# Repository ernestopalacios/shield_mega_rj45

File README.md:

shiel_mega_rj45
===============

Shield for arduino mega I/O using RJ45 connectors

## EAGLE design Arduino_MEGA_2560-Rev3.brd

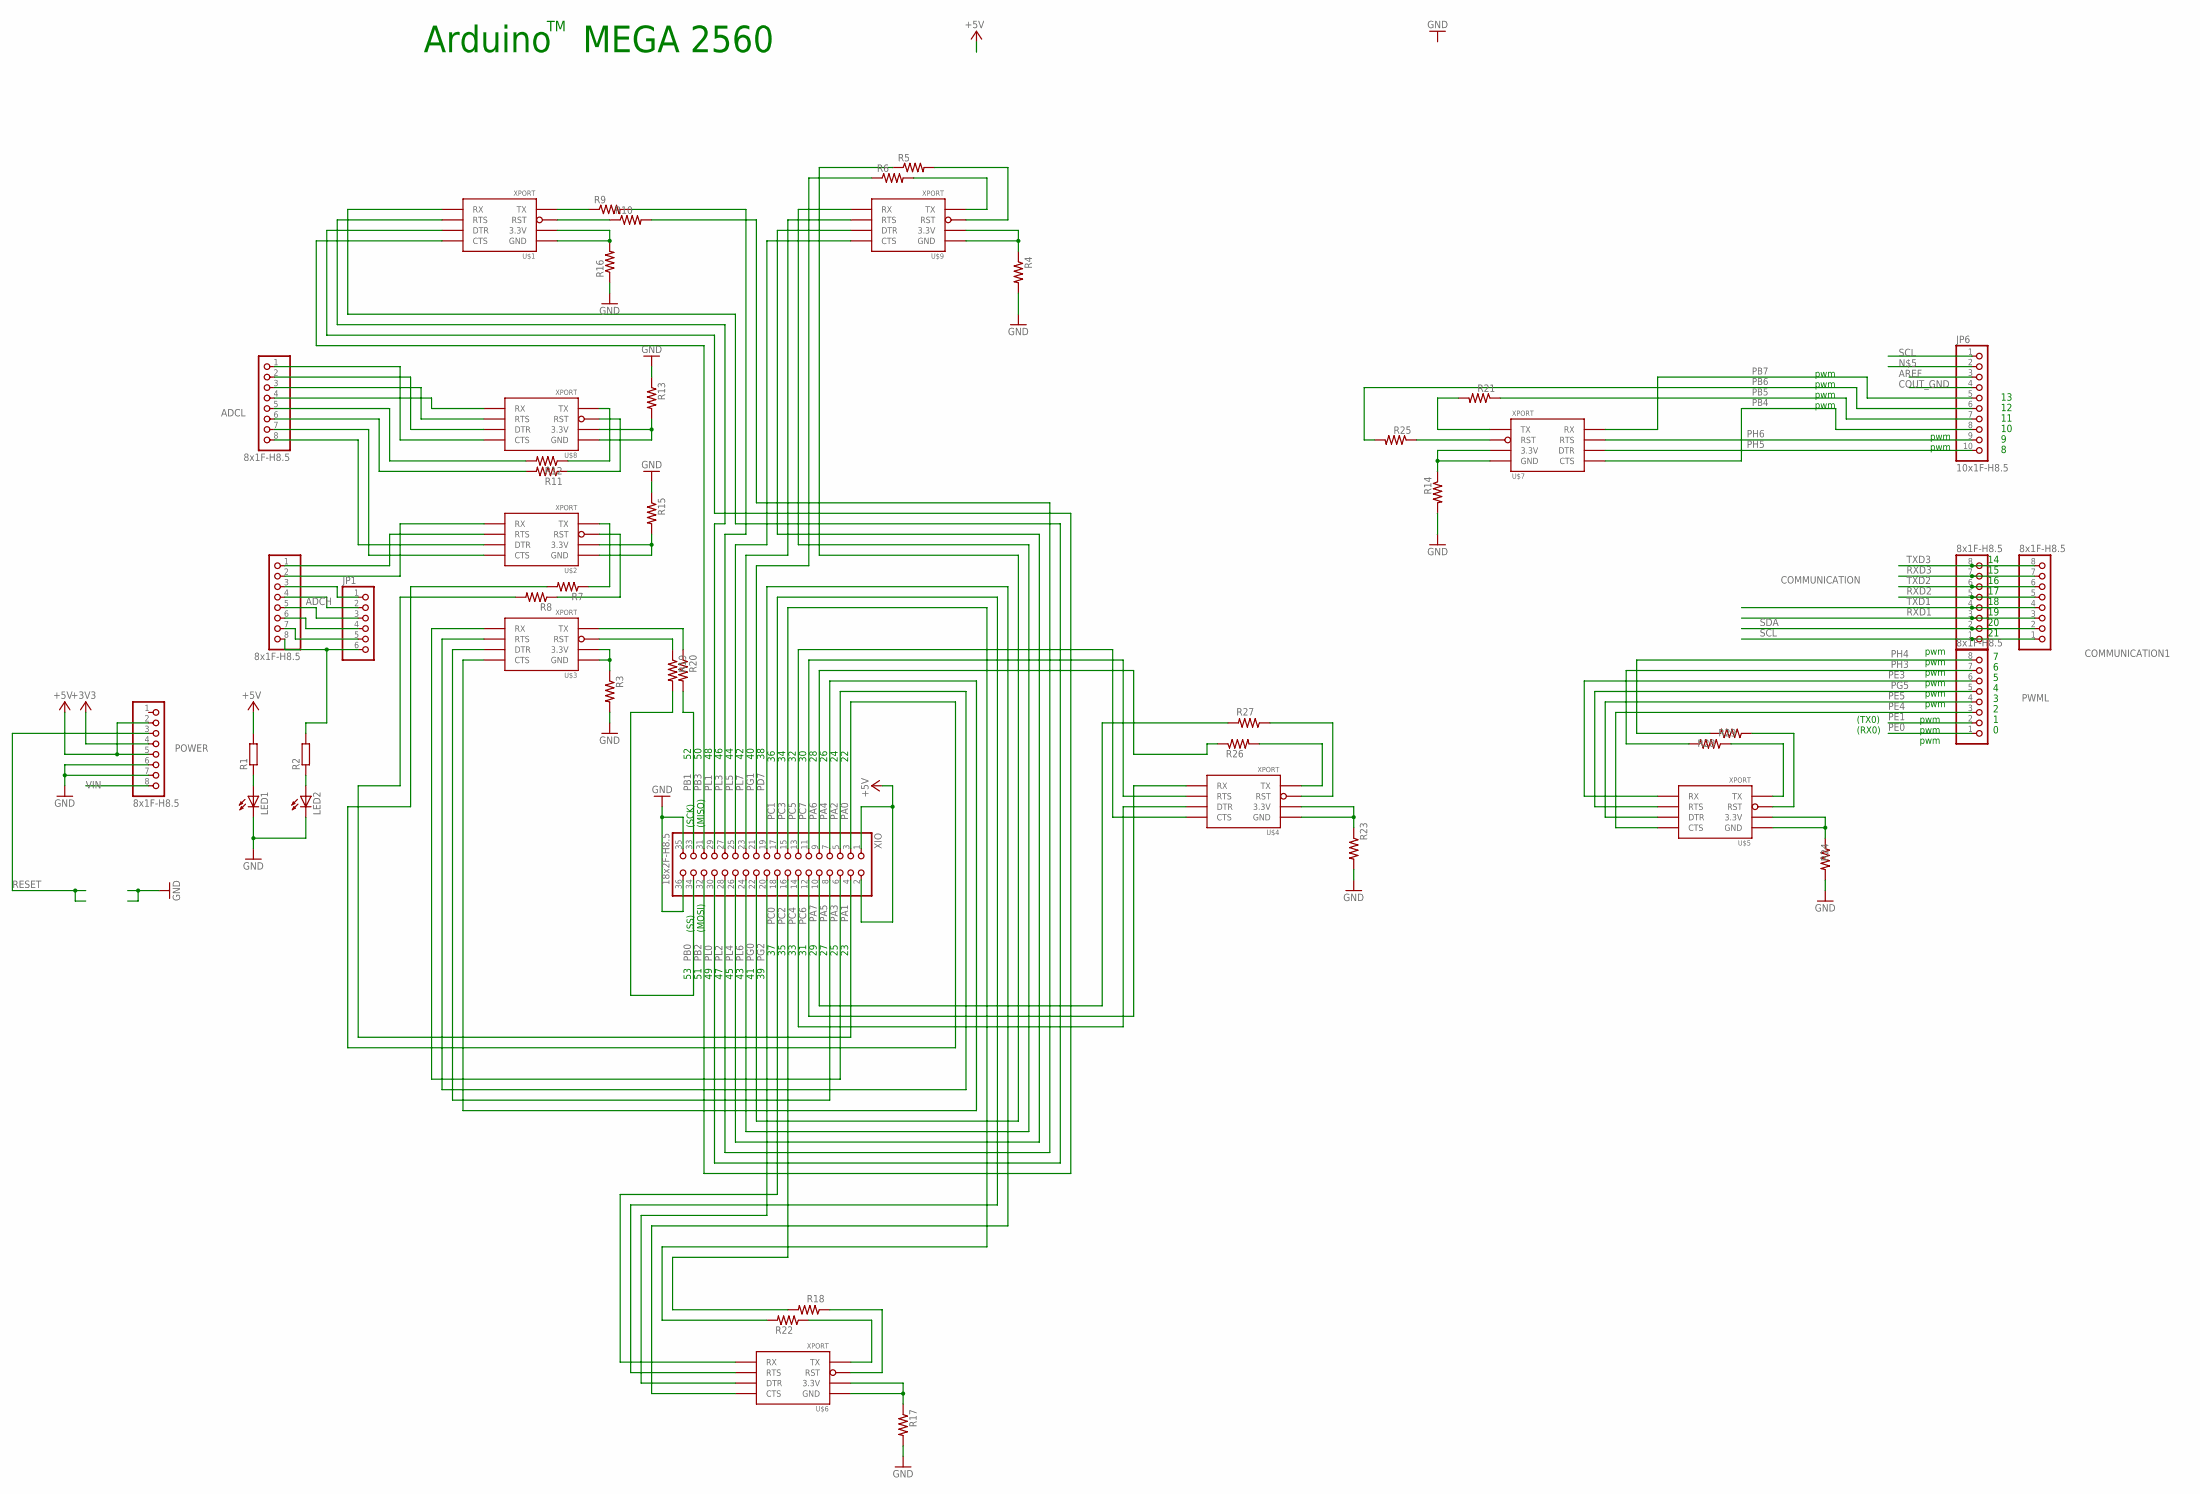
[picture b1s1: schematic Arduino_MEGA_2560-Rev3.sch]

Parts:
ADCH: 8x1F-H8.5; 1X08
ADCL: 8x1F-H8.5; 1X08
COMMUNICATION, COMMUNICATION1: 8x1F-H8.5; 1X08
JP1: PINHD-1X6; 1X06
JP6: 10x1F-H8.5; 1X10
LED1, LED2: LEDCHIPLED_1206; CHIPLED_1206
POWER: 8x1F-H8.5; 1X08
PWML: 8x1F-H8.5; 1X08
R1, R2: R-EU_M1206; M1206
R3, R7, R8, R11, R12, R13, R14, R15, R19, R20: R-US_0207/10; 0207/10
R4, R5, R6, R9, R10, R16, R17, R18, R22, R23, R24, R26, R27, R28, R29: R-US_0207/15; 0207/15
R21, R25: R-US_0207/2V; 0207/2V
U$1, U$2, U$3, U$4, U$5, U$6, U$7, U$8, U$9: XPORT
XIO: 18x2F-H8.5; 2X18

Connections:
+3V3: POWER.4
+5V: POWER.2, POWER.5, R1.2, XIO.1, XIO.2
AREF: JP6.3
COUT_GND: JP6.4, LED1.C, LED2.C, POWER.6, POWER.7, R3.2, R4.2, R13.1, R14.2, R15.1, R16.1, R17.2, R23.2, R24.2, XIO.35, XIO.36
unnamed: LED1.A, R1.1
unnamed: LED2.A, R2.1
unnamed: ADCH.1, U$2.P6 (RTS)
unnamed: ADCH.2, U$2.P5 (RX)
unnamed: R14.1, U$7.P1 (GND), U$7.P2 (3.3V)
unnamed: ADCL.1, U$8.P8 (CTS)
unnamed: ADCL.2, U$8.P7 (DTR)
unnamed: ADCL.3, U$8.P6 (RTS)
unnamed: ADCH.3, JP1.1
unnamed: ADCL.4, U$8.P5 (RX)
unnamed: ADCL.5, R12.2
unnamed: ADCL.6, R11.2
unnamed: ADCL.7, U$2.P8 (CTS)
unnamed: ADCL.8, U$2.P7 (DTR)
unnamed: R15.2, U$2.P1 (GND), U$2.P2 (3.3V)
unnamed: R3.1, U$3.P1 (GND), U$3.P2 (3.3V)
unnamed: R4.1, U$9.P1 (GND), U$9.P2 (3.3V)
unnamed: R5.2, U$9.P3 (RST)
unnamed: R6.2, U$9.P4 (TX)
unnamed: ADCH.4, JP1.2
unnamed: ADCH.5, JP1.3
unnamed: ADCH.6, JP1.4
unnamed: ADCH.7, JP1.5
unnamed: ADCH.8, JP1.6, R2.2
unnamed: R16.2, U$1.P1 (GND), U$1.P2 (3.3V)
unnamed: R10.1, U$1.P3 (RST)
unnamed: R9.1, U$1.P4 (TX)
unnamed: R17.1, U$6.P1 (GND), U$6.P2 (3.3V)
unnamed: R7.1, U$2.P4 (TX)
unnamed: R8.1, U$2.P3 (RST)
unnamed: R22.1, U$6.P4 (TX)
unnamed: R18.1, U$6.P3 (RST)
unnamed: R24.1, U$5.P1 (GND), U$5.P2 (3.3V)
unnamed: R23.1, U$4.P1 (GND), U$4.P2 (3.3V)
unnamed: R19.1, U$3.P3 (RST)
unnamed: R20.2, XIO.33
unnamed: R21.2, U$7.P4 (TX)
unnamed: R25.1, U$7.P3 (RST)
unnamed: R28.1, U$5.P4 (TX)
unnamed: R29.1, U$5.P3 (RST)
unnamed: R26.2, U$4.P4 (TX)
unnamed: R27.1, U$4.P3 (RST)
unnamed: R11.1, U$8.P3 (RST)
unnamed: R12.1, U$8.P4 (TX)
unnamed: R13.2, U$8.P1 (GND), U$8.P2 (3.3V)
PA0: R7.2, XIO.3
PA1: R8.2, XIO.4
PA2: U$3.P6 (RTS), XIO.5
PA3: U$3.P5 (RX), XIO.6
PA4: U$3.P8 (CTS), XIO.7
PA5: U$3.P7 (DTR), XIO.8
PA6: R26.1, XIO.9
PA7: R27.2, XIO.10
PB0: R19.2, XIO.34
PB1: R20.1, U$3.P4 (TX)
PB2: U$1.P7 (DTR), XIO.32
PB3: U$1.P8 (CTS), XIO.31
PB4: JP6.8, U$7.P8 (CTS)
PB5: JP6.7, R21.1
PB6: JP6.6, R25.2
PB7: JP6.5, U$7.P5 (RX)
PC0: U$6.P5 (RX), XIO.18
PC1: U$6.P6 (RTS), XIO.17
PC2: R18.2, XIO.16
PC3: R22.2, XIO.15
PC4: U$4.P7 (DTR), XIO.14
PC5: U$4.P8 (CTS), XIO.13
PC6: U$4.P5 (RX), XIO.12
PC7: U$4.P6 (RTS), XIO.11
PD7: U$6.P8 (CTS), XIO.19
PE0: PWML.1
PE1: PWML.2
PE3: PWML.6, U$5.P5 (RX)
PE4: PWML.3, U$5.P8 (CTS)
PE5: PWML.4, U$5.P7 (DTR)
PG0: R5.1, XIO.22
PG1: R6.1, XIO.21
PG2: U$6.P7 (DTR), XIO.20
PG5: PWML.5, U$5.P6 (RTS)
PH3: PWML.7, R28.2
PH4: PWML.8, R29.2
PH5: JP6.10, U$7.P7 (DTR)
PH6: JP6.9, U$7.P6 (RTS)
PL0: U$1.P5 (RX), XIO.30
PL1: U$1.P6 (RTS), XIO.29
PL2: R10.2, XIO.28
PL3: R9.2, XIO.27
PL4: U$9.P7 (DTR), XIO.26
PL5: U$9.P8 (CTS), XIO.25
PL6: U$9.P5 (RX), XIO.24
PL7: U$9.P6 (RTS), XIO.23
RESET: POWER.3
RXD1: COMMUNICATION.3, COMMUNICATION1.3
RXD2: COMMUNICATION.5, COMMUNICATION1.5
RXD3: COMMUNICATION.7, COMMUNICATION1.7
SCL: COMMUNICATION.1, COMMUNICATION1.1, JP6.1
SDA: COMMUNICATION.2, COMMUNICATION1.2
TXD1: COMMUNICATION.4, COMMUNICATION1.4
TXD2: COMMUNICATION.6, COMMUNICATION1.6
TXD3: COMMUNICATION.8, COMMUNICATION1.8
VIN: POWER.8

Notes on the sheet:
Arduino MEGA 2560
pwm
(TX0)
(RX0)
(SS)
(MOSI)
(SCK)
(MISO)

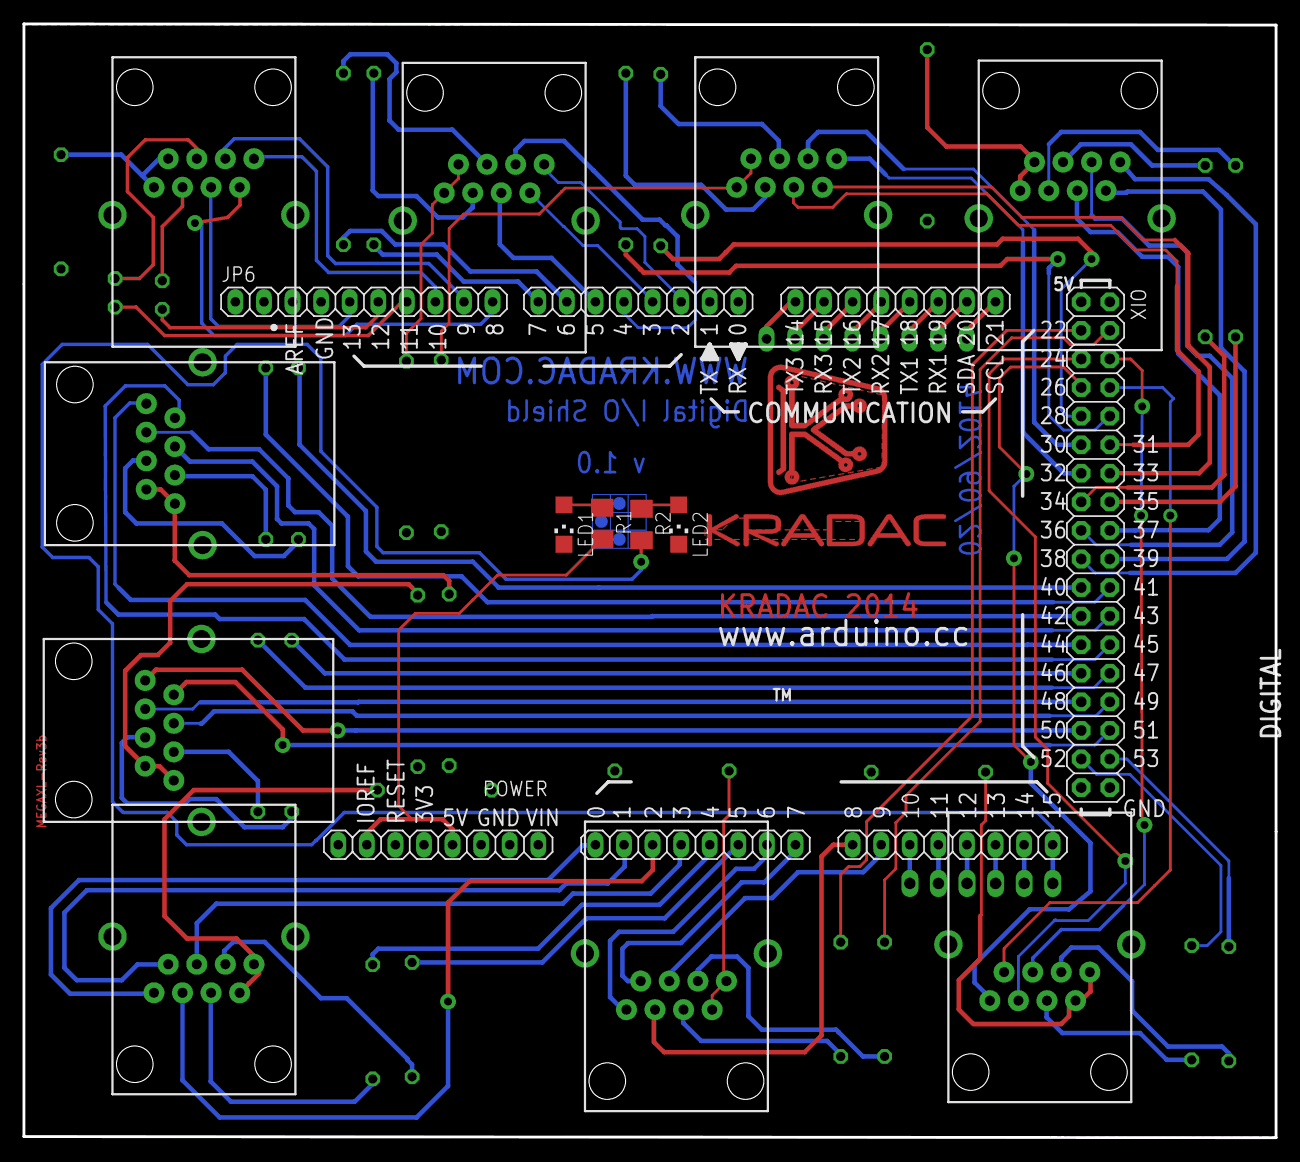
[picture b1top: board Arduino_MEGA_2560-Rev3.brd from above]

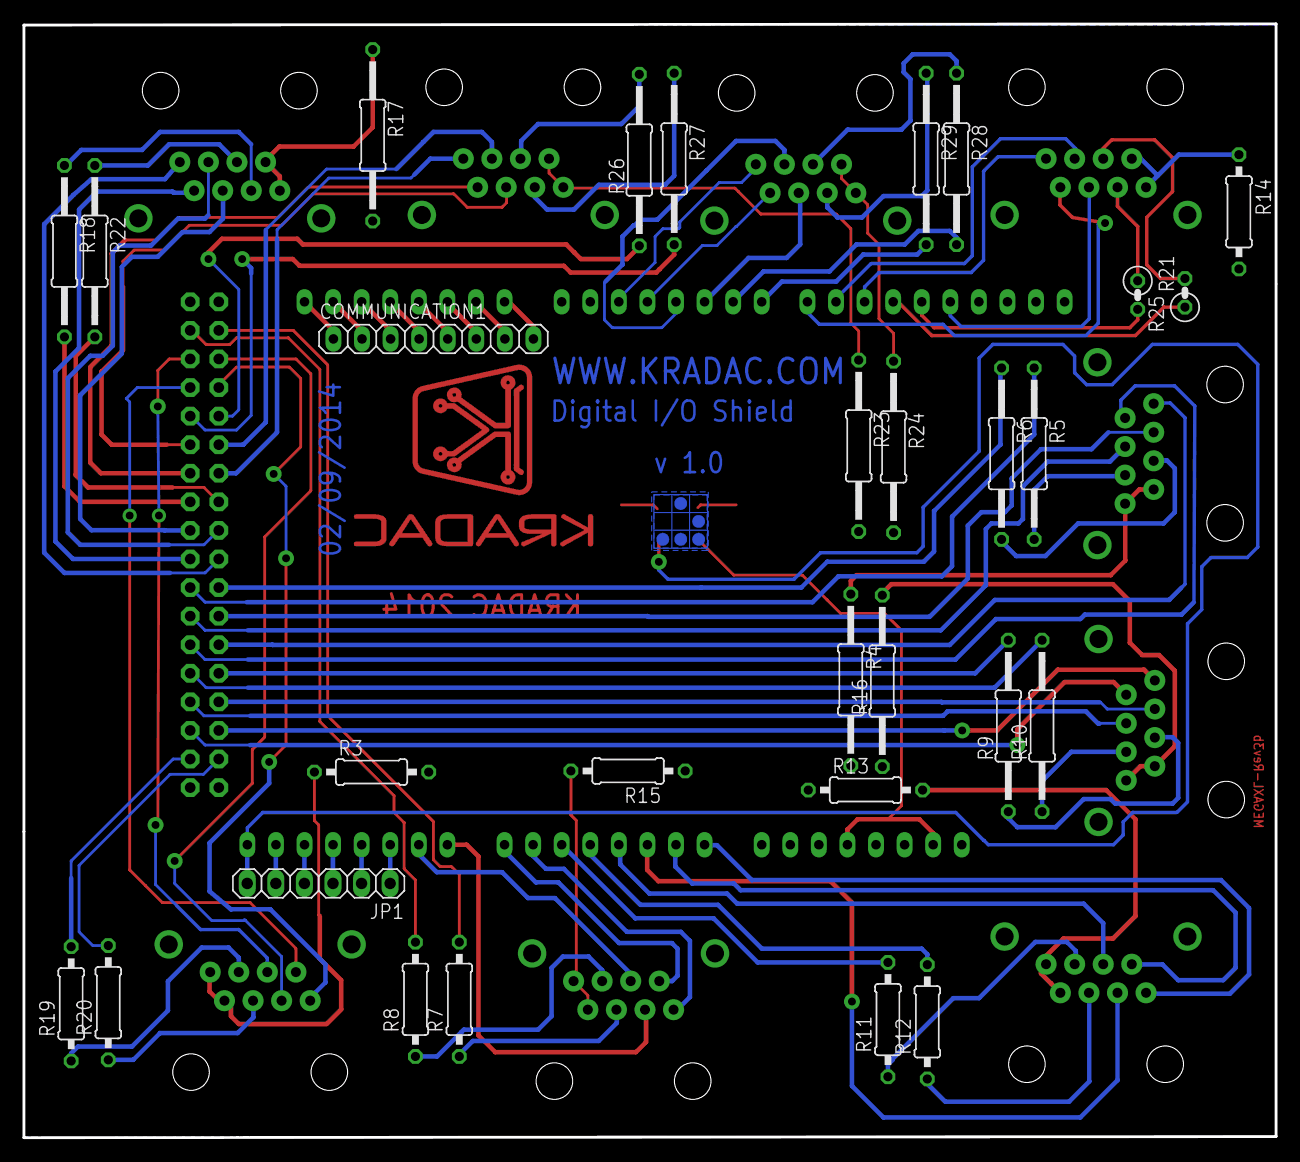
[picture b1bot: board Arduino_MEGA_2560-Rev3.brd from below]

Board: 2 copper layers, 111.3 x 99.0 mm, 49 parts (29 on the bottom side), 99 nets.

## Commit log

2014-08-23 Documentos descargados desde arduino.cc
2014-08-24 Version inicial del Shield
2014-08-27 nuevas dimensiones placa
2014-08-28 nuevas resistencias, revisar los pines de entrada salida
2014-09-02 Version 0.1 - Faltan planos de tierra
2014-09-03 Terminada la version 1.0
2014-09-03 Añadido emblema Hacker

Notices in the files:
parts and their libraries:
SparkFun-Boards: Licensing: Creative Commons ShareAlike 4.0 International - https://creativecommons.org/licenses/by-sa/4.0
